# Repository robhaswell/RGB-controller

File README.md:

# RGB-controller
A 10-channel RGB controller based on the ESP32 microcontroller

**Important:** I have successfully ordered and assembled this project, but since then I altered the 47uF capacitor package so that it is not an *extended part* at JLCPCB. The author accepts NO RESPONSIBILITY for this product working, and it has not undergone extensive safety testing. Use at your own risk.

# Ordering the PCB
To order the PCB at [JLCPCB](https://jlcpcb.com) you will need to do the following steps:

1. Submit `/gerber.zip` as your job
2. Choose the following options:
    1. PCB Color: Black
    2. Remove Order Number: Specify a location
3. Enable SMT Assembly and choose:
    1. Top side
    2. SMT QTY: 2 or 5 depending on your needs.
    3. Tooling holes: Added by Customer
4. Confirm
5. Upload files:
    1. BOM File: `/JLC/Controller.csv`
    2. CPL File: `/JLC/Controller-top-pos.csv`
6. Click through to the end
7. To order the top and bottom plates (high recommended), make two more orders with `plates/gerber-top.zip` and `plates/gerber-bottom.zip` - no SMT Assembly required
    1. PCB Thickness: Can be as low as 1.0mm but I recommend leaving it at 1.6mm
    2. Remove Order Number: Not necessary, I recommend No, but you could choose Yes

** **MAKE SURE YOU CHOOSE THE CHEAPEST SHIPPING OPTION!!** **.

Final discounts will be applied right before you pay, including free SMT Assembly. The final cost should be around $30 but it varies.

## Components

Component | Quantity | Link
-|-|-
ESP32 Devkit v1 (DOIT) | 1 | https://www.aliexpress.com/item/1005001648850998.html
3-pin RGB needle adapter | 10 | https://www.aliexpress.com/item/1005005743425681.html
350211-1 Mate-N-Lok connector | 1 | Find these locally - search "350211-1" at your local electronics store, or check Ebay sellers in your area. You may know this better as a "Molex connector".
M2 standoff, 4mm, male-female | 12 or 20 | https://www.aliexpress.com/item/1005002542327479.html?spm=a2g0o.productlist.0.0.9c1c7ed6qyouL8&aem_p4p_detail=202106131120581657595816822930013487928 or locally. Order 20 if not using screws (see next).
Optional: M2 screws and nuts | 4 | You can also find these on Aliexpress, or with the above spacers in kits on Amazon, etc. To keep costs down you can use use 20 male-female standoffs, but screws + nuts (or 4x female-female standoffs) will be neater.

## Build
Soldering and construction order order I would recommend:

### 1. RGB headers
10x RGB pin headers should come first.
You will need to remove or clip one pin from each header.
To pull them out I recommend using pliers to push the pins through.
You can also grab the pin with pliers and use your iron to heat it from the other side, this will free it from the plastic.

Preparing these pin headers is by far the most time consuming part of the assembly.

**Protip**: Place all 10 pin headers on your PCB, then place one of your spare PCBs over the top.
You might want to line up the pin headers on one side, and then wiggle the binding ones until they enter the mounting holes.
This will help you to get 10x headers which are nicely lined up and evenly spaced.

### 2. PCB standoffs
Most standoffs do not pass through the holes on the ESP32 devkit, so they will need adding to the PCB before the ESP32 devkit is soldered on top.

### 3. ESP32 devkit
Next, solder this to the board using the included pin headers. You might optionally want to use the standoffs to fix it to the PCB while soldering. You will also need to clip the headers after it is soldered.

### 4. 350211-1 Mate-N-Lok connector ("Molex connector")
Finally you can solder the power connector, make sure to use plenty of solder on this one.

### 5. Screw it all together
Screw on your top and bottom plates. These will be important in protecting your RGB controller and preventing shorts.

## Loading the firmware
The final step is to load the firmware in accordance with instructions on the WLED wiki: https://github.com/Aircoookie/WLED/wiki

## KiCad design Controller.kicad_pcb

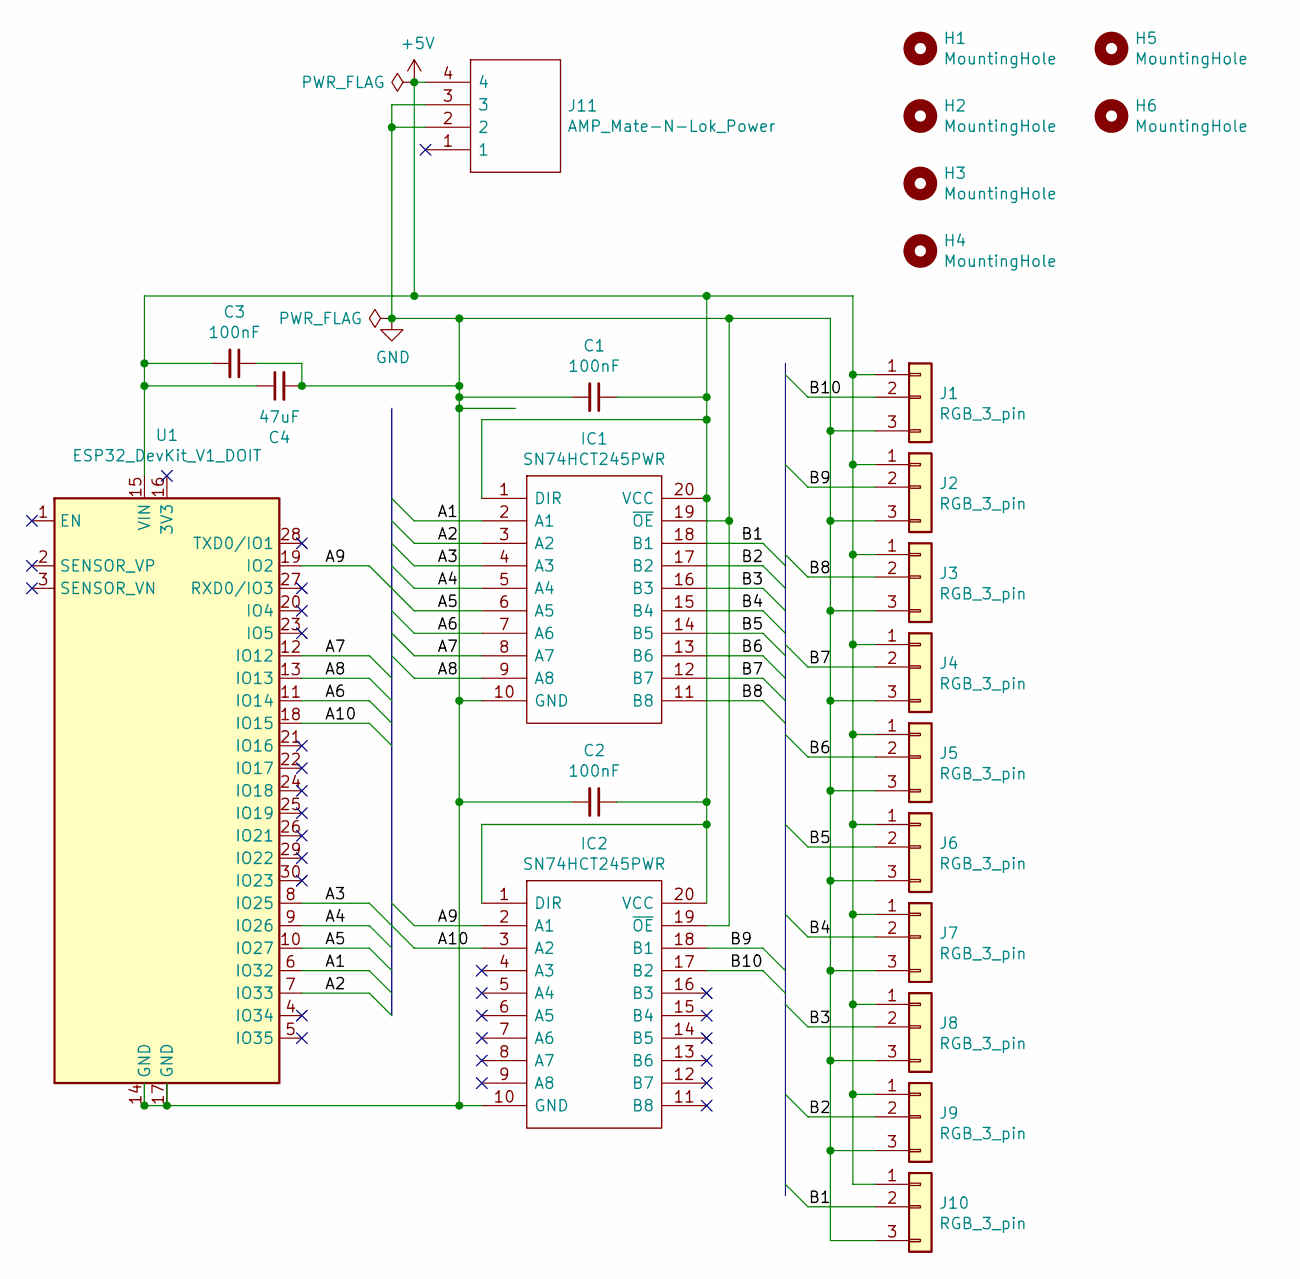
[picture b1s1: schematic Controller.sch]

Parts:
C1, C2, C3: 100nF; C_0603_1608Metric
C4: 47uF; C_1206_3216Metric
H1, H2, H3, H4: MountingHole; MountingHole_2.2mm_M2
H5, H6: MountingHole; ToolingHole_1.152mm
IC1, IC2: SN74HCT245PWR; TSSOP-20_4.4x6.5mm_P0.65mm; Manufacturer_Part_Number SN74HCT245PWR; Mouser Part Number 595-SN74HCT245PWR
J1, J2, J3, J4, J5, J6, J7, J8, J9, J10: RGB_3_pin; RGB_3-Pin
J11: AMP_Mate-N-Lok_Power; TE_MATE-N-LOK_1-794374-x_1x01_P4.14mm_Horizontal; Manufacturer_Part_Number 350211-1
U1: ESP32_DevKit_V1_DOIT; esp32_devkit_v1_doit

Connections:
+5V: C1.1, C2.1, C3.2, C4.1, IC1.1 (DIR), IC1.20 (VCC), IC2.1 (DIR), IC2.20 (VCC), J1.1, J2.1, J3.1, J4.1, J5.1, J6.1, J7.1, J8.1, J9.1, J10.1, J11.4, U1.15 (VIN)
/A1: IC1.2 (A1), U1.6 (IO32)
/A2: IC1.3 (A2), U1.7 (IO33)
/A3: IC1.4 (A3), U1.8 (IO25)
/A4: IC1.5 (A4), U1.9 (IO26)
/A5: IC1.6 (A5), U1.10 (IO27)
/A6: IC1.7 (A6), U1.11 (IO14)
/A7: IC1.8 (A7), U1.12 (IO12)
/A8: IC1.9 (A8), U1.13 (IO13)
/A9: IC2.2 (A1), U1.19 (IO2)
/A10: IC2.3 (A2), U1.18 (IO15)
/B1: IC1.18 (B1), J10.2
/B2: IC1.17 (B2), J9.2
/B3: IC1.16 (B3), J8.2
/B4: IC1.15 (B4), J7.2
/B5: IC1.14 (B5), J6.2
/B6: IC1.13 (B6), J5.2
/B7: IC1.12 (B7), J4.2
/B8: IC1.11 (B8), J3.2
/B9: IC2.18 (B1), J2.2
/B10: IC2.17 (B2), J1.2
GND: C1.2, C2.2, C3.1, C4.2, IC1.10 (GND), IC1.19 (~OE), IC2.10 (GND), IC2.19 (~OE), J1.3, J2.3, J3.3, J4.3, J5.3, J6.3, J7.3, J8.3, J9.3, J10.3, J11.2, J11.3, U1.14 (GND), U1.17 (GND)

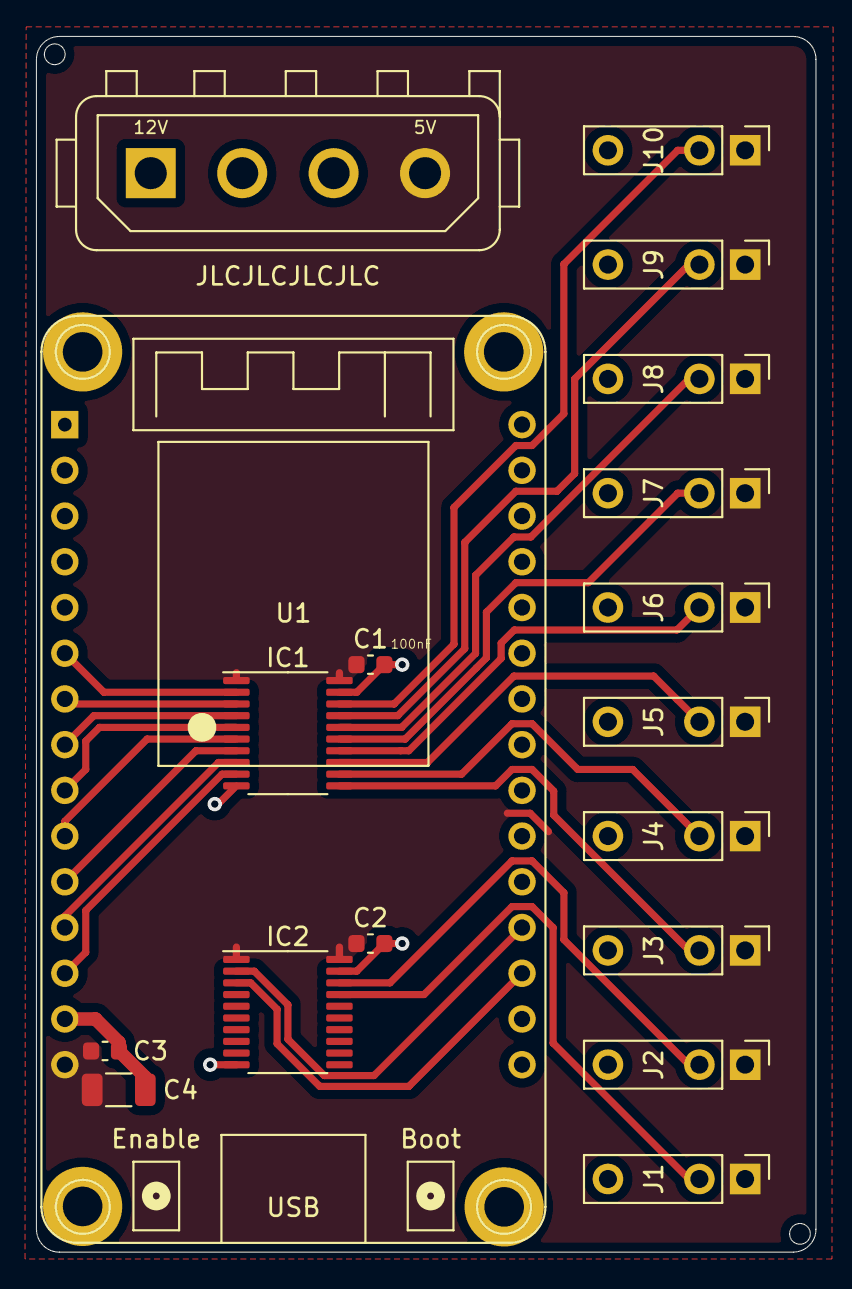
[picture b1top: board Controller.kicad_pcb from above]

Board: 2 copper layers, 43.3 x 67.5 mm, 24 parts (0 on the bottom side), 22 nets.

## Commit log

2021-03-21 Initial commit.
2021-03-21 * Incoporate feedback * The ESP32 takes 12V on VIN
2021-03-22 Update to match parts available at JCL.
2021-03-22 Rename project and create manufacturing files.
2021-03-22 Add top and bottom plate files.
2021-03-23 Files for the case.
2021-03-25 Pictures.
2021-04-26 Backup schematics for ESP32.
2021-04-26 Project config from platformio.
2021-04-26 Basic firmware which sets LED values, connects to WiFi and enables OTA updates.
2021-05-01 Upload via network.
2021-05-01 Remove autogenerated files from repo.
2021-05-01 Hide wifi configuration and prevent autogenerated files from being added to the repo.
2021-05-01 Minimally acceptable synthwave colouring.
2021-05-01 More better synthwave.
2021-05-01 Bring out the reservoir in full blue.
2021-05-01 Brighter GPU orange.
2021-05-03 Tweak colours.
2021-05-04 Add some notes on components.
2021-05-04 More compact layout with 10 channels.
2021-05-16 Update controller to new design.
2021-05-16 Reorganise JLC exports.
2021-05-16 Update the README with new images.
2021-05-16 Images, documentation and resources.
2021-05-16 Manufacturing files.
2021-05-16 Top and bottom plates.
2021-06-13 Port firmware to WLED but add a note.
2021-06-13 Use 47uF capacitor which is available in JLC's basic library.
2021-06-13 README updates.
2021-06-13 Safety notice.
2021-06-13 Emphasis.
2021-06-13 Adjust SMT quantity.
